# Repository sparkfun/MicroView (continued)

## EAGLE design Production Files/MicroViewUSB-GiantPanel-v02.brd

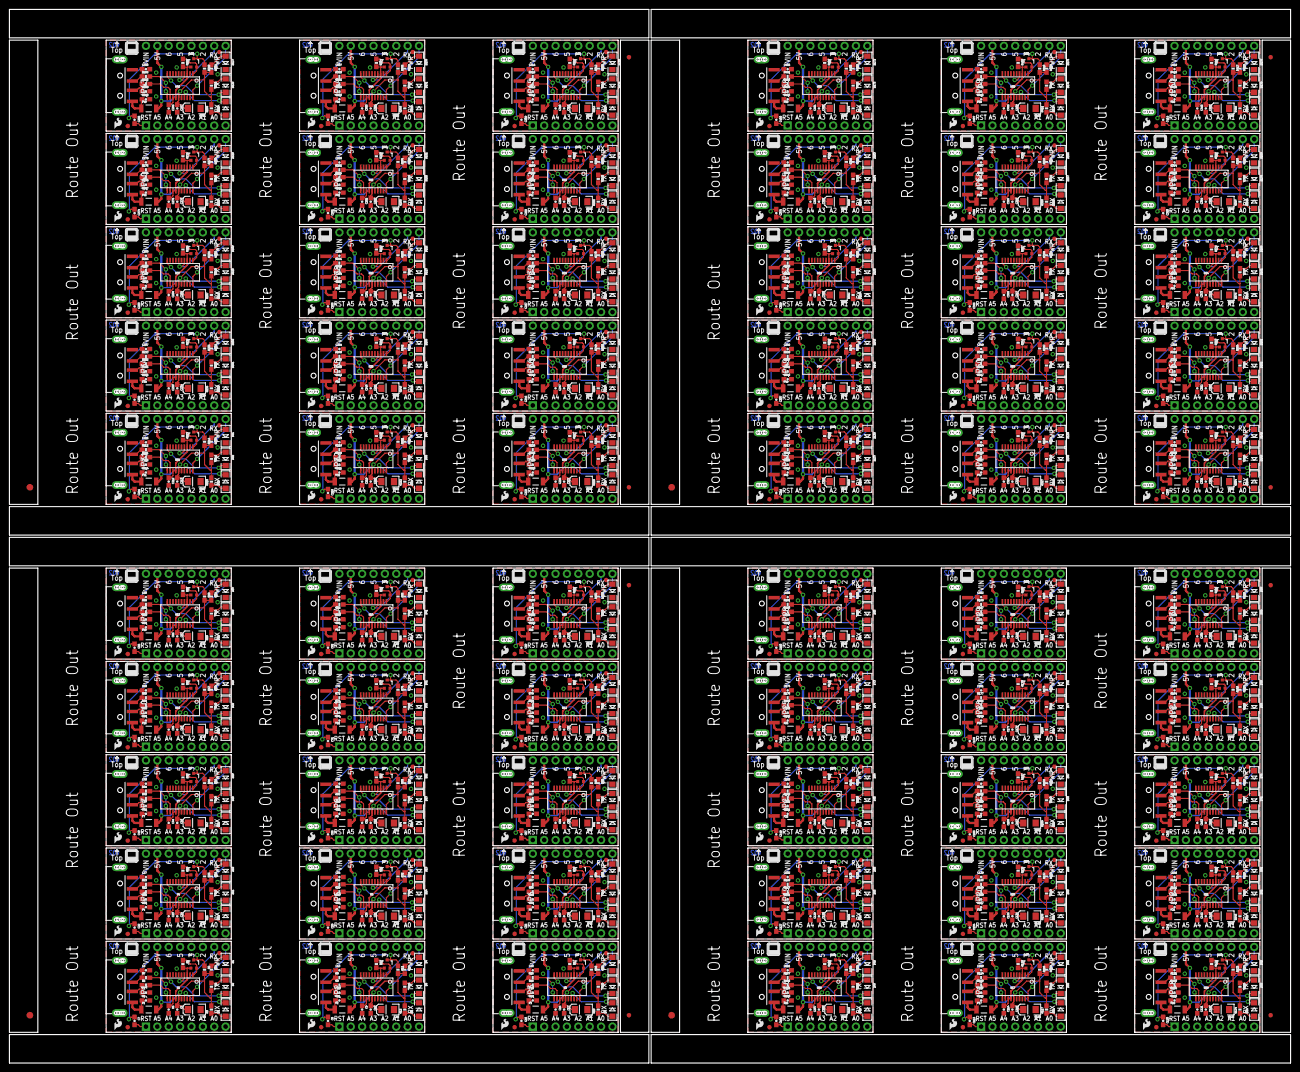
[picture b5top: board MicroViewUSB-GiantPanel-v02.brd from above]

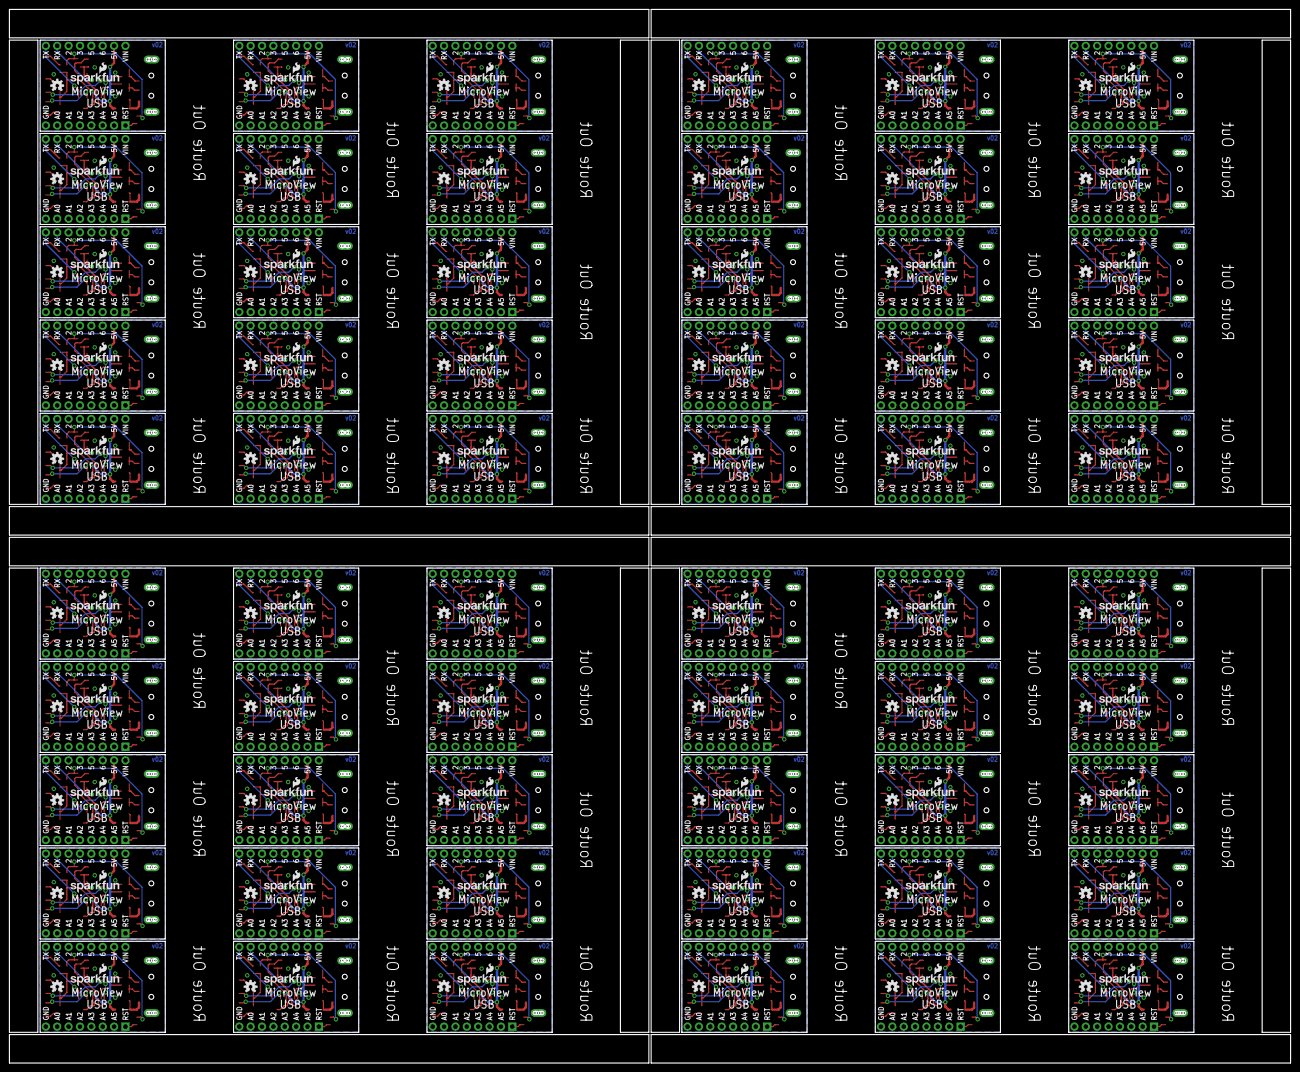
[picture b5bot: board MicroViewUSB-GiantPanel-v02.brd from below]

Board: 2 copper layers, 286.0 x 235.2 mm, 1632 parts (120 on the bottom side), 1080 nets.

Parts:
C1, C5, C6, C7, C8, C9, C10, C11, C15, C16, C17, C18, C22, C23, C24, C25, C29, C30, C31, C32, C36, C37, C38, C39, C43, C44, C45, C46, C50, C51, C52, C53, C57, C58, C59, C60, C64, C65, C66, C67, C71, C72, C73, C74, C78, C79, C80, C81, C85, C86, C87, C88, C92, C93, C94, C95, C99, C100, C101, C102, C106, C107, C108, C109, C113, C114, C115, C116, C120, C121, C122, C123, C127, C128, C129, C130, C134, C135, C136, C137, C141, C142, C143, C144, C148, C149, C150, C151, C155, C156, C157, C158, C162, C163, C164, C165, C169, C170, C171, C172, C176, C177, C178, C179, C183, C184, C185, C186, C190, C191, C192, C193, C197, C198, C199, C200, C204, C205, C206, C207, C211, C212, C213, C214, C218, C219, C220, C221, C225, C226, C227, C228, C232, C233, C234, C235, C239, C240, C241, C242, C246, C247, C248, C249, C253, C254, C255, C256, C260, C261, C262, C263, C267, C268, C269, C270, C274, C275, C276, C277, C281, C282, C283, C284, C288, C289, C290, C291, C295, C296, C297, C298, C302, C303, C304, C305, C309, C310, C311, C312, C316, C317, C318, C319, C323, C324, C325, C326, C330, C331, C332, C333, C337, C338, C339, C340, C344, C345, C346, C347, C351, C352, C353, C354, C358, C359, C360, C361, C365, C366, C367, C368, C372, C373, C374, C375, C379, C380, C381, C382, C386, C387, C388, C389, C393, C394, C395, C396, C400, C401, C402, C403, C407, C408, C409, C410, C414, C415, C416, C417: 0.1uF; 0603-CAP
C2, C3, C12, C13, C19, C20, C26, C27, C33, C34, C40, C41, C47, C48, C54, C55, C61, C62, C68, C69, C75, C76, C82, C83, C89, C90, C96, C97, C103, C104, C110, C111, C117, C118, C124, C125, C131, C132, C138, C139, C145, C146, C152, C153, C159, C160, C166, C167, C173, C174, C180, C181, C187, C188, C194, C195, C201, C202, C208, C209, C215, C216, C222, C223, C229, C230, C236, C237, C243, C244, C250, C251, C257, C258, C264, C265, C271, C272, C278, C279, C285, C286, C292, C293, C299, C300, C306, C307, C313, C314, C320, C321, C327, C328, C334, C335, C341, C342, C348, C349, C355, C356, C362, C363, C369, C370, C376, C377, C383, C384, C390, C391, C397, C398, C404, C405, C411, C412, C418, C419: 47pF; 0603-CAP
C4, C14, C21, C28, C35, C42, C49, C56, C63, C70, C77, C84, C91, C98, C105, C112, C119, C126, C133, C140, C147, C154, C161, C168, C175, C182, C189, C196, C203, C210, C217, C224, C231, C238, C245, C252, C259, C266, C273, C280, C287, C294, C301, C308, C315, C322, C329, C336, C343, C350, C357, C364, C371, C378, C385, C392, C399, C406, C413, C420: 10uF; EIA3216
D1, D4, D7, D10, D13, D16, D19, D22, D25, D28, D31, D34, D37, D40, D43, D46, D49, D52, D55, D58, D61, D64, D67, D70, D73, D76, D79, D82, D85, D88, D91, D94, D97, D100, D103, D106, D109, D112, D115, D118, D121, D124, D127, D130, D133, D136, D139, D142, D145, D148, D151, D154, D157, D160, D163, D166, D169, D172, D175, D178: GREEN; LED-1206
D2, D5, D8, D11, D14, D17, D20, D23, D26, D29, D32, D35, D38, D41, D44, D47, D50, D53, D56, D59, D62, D65, D68, D71, D74, D77, D80, D83, D86, D89, D92, D95, D98, D101, D104, D107, D110, D113, D116, D119, D122, D125, D128, D131, D134, D137, D140, D143, D146, D149, D152, D155, D158, D161, D164, D167, D170, D173, D176, D179: RED; LED-1206
D3, D6, D9, D12, D15, D18, D21, D24, D27, D30, D33, D36, D39, D42, D45, D48, D51, D54, D57, D60, D63, D66, D69, D72, D75, D78, D81, D84, D87, D90, D93, D96, D99, D102, D105, D108, D111, D114, D117, D120, D123, D126, D129, D132, D135, D138, D141, D144, D147, D150, D153, D156, D159, D162, D165, D168, D171, D174, D177, D180: Yellow; LED-1206
E$1, E$4, E$9, E$12: FIDUCIAL-1.5X3
E$2, E$3, E$5, E$6, E$7, E$8, E$10, E$11: FIDUCIAL-1X2
F1, F2, F3, F4, F5, F6, F7, F8, F9, F10, F11, F12, F13, F14, F15, F16, F17, F18, F19, F20, F21, F22, F23, F24, F25, F26, F27, F28, F29, F30, F31, F32, F33, F34, F35, F36, F37, F38, F39, F40, F41, F42, F43, F44, F45, F46, F47, F48, F49, F50, F51, F52, F53, F54, F55, F56, F57, F58, F59, F60: 500mA; PTC-1206-WIDE
FID1, FID2, FID3, FID4, FID5, FID6, FID7, FID8, FID9, FID10, FID11, FID12, FID13, FID14, FID15, FID16, FID17, FID18, FID19, FID20, FID21, FID22, FID23, FID24, FID25, FID26, FID27, FID28, FID29, FID30, FID31, FID32, FID33, FID34, FID35, FID36, FID37, FID38, FID39, FID40, FID41, FID42, FID43, FID44, FID45, FID46, FID47, FID48, FID49, FID50, FID51, FID52, FID53, FID54, FID55, FID56, FID57, FID58, FID59, FID60, FID61, FID62, FID63, FID64, FID65, FID66, FID67, FID68, FID69, FID70, FID71, FID72, FID73, FID74, FID75, FID76, FID77, FID78, FID79, FID80, FID81, FID82, FID83, FID84, FID85, FID86, FID87, FID88, FID89, FID90, FID91, FID92, FID93, FID94, FID95, FID96, FID97, FID98, FID99, FID100, FID101, FID102, FID103, FID104, FID105, FID106, FID107, FID108, FID109, FID110, FID111, FID112, FID113, FID114, FID115, FID116, FID117, FID118, FID119, FID120: FIDUCIAL1X2; FIDUCIAL-1X2
J1, J2, J3, J4, J5, J6, J7, J8, J9, J10, J11, J12, J13, J14, J15, J16, J17, J18, J19, J20, J21, J22, J23, J24, J25, J26, J27, J28, J29, J30, J31, J32, J33, J34, J35, J36, J37, J38, J39, J40, J41, J42, J43, J44, J45, J46, J47, J48, J49, J50, J51, J52, J53, J54, J55, J56, J57, J58, J59, J60: MICROVIEW-16ND; MV-DIP16-NODIMENSION
JP1, JP2, JP3, JP4, JP5, JP6, JP7, JP8, JP9, JP10, JP11, JP12, JP13, JP14, JP15, JP16, JP17, JP18, JP19, JP20, JP21, JP22, JP23, JP24, JP25, JP26, JP27, JP28, JP29, JP30, JP31, JP32, JP33, JP34, JP35, JP36, JP37, JP38, JP39, JP40, JP41, JP42, JP43, JP44, JP45, JP46, JP47, JP48, JP49, JP50, JP51, JP52, JP53, JP54, JP55, JP56, JP57, JP58, JP59, JP60: USBA-SMD-MALE; USB-A-SMT-MALE
LOGO1, LOGO5, LOGO8, LOGO11, LOGO14, LOGO17, LOGO20, LOGO23, LOGO26, LOGO29, LOGO32, LOGO35, LOGO38, LOGO41, LOGO44, LOGO47, LOGO50, LOGO53, LOGO56, LOGO59, LOGO62, LOGO65, LOGO68, LOGO71, LOGO74, LOGO77, LOGO80, LOGO83, LOGO86, LOGO89, LOGO92, LOGO95, LOGO98, LOGO101, LOGO104, LOGO107, LOGO110, LOGO113, LOGO116, LOGO119, LOGO122, LOGO125, LOGO128, LOGO131, LOGO134, LOGO137, LOGO140, LOGO143, LOGO146, LOGO149, LOGO152, LOGO155, LOGO158, LOGO161, LOGO164, LOGO167, LOGO170, LOGO173, LOGO176, LOGO179: SFE_LOGO_FLAME.1_INCH; SFE_LOGO_FLAME_.1
LOGO2, LOGO4, LOGO7, LOGO10, LOGO13, LOGO16, LOGO19, LOGO22, LOGO25, LOGO28, LOGO31, LOGO34, LOGO37, LOGO40, LOGO43, LOGO46, LOGO49, LOGO52, LOGO55, LOGO58, LOGO61, LOGO64, LOGO67, LOGO70, LOGO73, LOGO76, LOGO79, LOGO82, LOGO85, LOGO88, LOGO91, LOGO94, LOGO97, LOGO100, LOGO103, LOGO106, LOGO109, LOGO112, LOGO115, LOGO118, LOGO121, LOGO124, LOGO127, LOGO130, LOGO133, LOGO136, LOGO139, LOGO142, LOGO145, LOGO148, LOGO151, LOGO154, LOGO157, LOGO160, LOGO163, LOGO166, LOGO169, LOGO172, LOGO175, LOGO178: OSHW-LOGOS; OSHW-LOGO-S
LOGO3, LOGO6, LOGO9, LOGO12, LOGO15, LOGO18, LOGO21, LOGO24, LOGO27, LOGO30, LOGO33, LOGO36, LOGO39, LOGO42, LOGO45, LOGO48, LOGO51, LOGO54, LOGO57, LOGO60, LOGO63, LOGO66, LOGO69, LOGO72, LOGO75, LOGO78, LOGO81, LOGO84, LOGO87, LOGO90, LOGO93, LOGO96, LOGO99, LOGO102, LOGO105, LOGO108, LOGO111, LOGO114, LOGO117, LOGO120, LOGO123, LOGO126, LOGO129, LOGO132, LOGO135, LOGO138, LOGO141, LOGO144, LOGO147, LOGO150, LOGO153, LOGO156, LOGO159, LOGO162, LOGO165, LOGO168, LOGO171, LOGO174, LOGO177, LOGO180: SFE_LOGO_NAME_FLAME.1_INCH; SFE_LOGO_NAME_FLAME_.1
Q1, Q2, Q3, Q4, Q5, Q6, Q7, Q8, Q9, Q10, Q11, Q12, Q13, Q14, Q15, Q16, Q17, Q18, Q19, Q20, Q21, Q22, Q23, Q24, Q25, Q26, Q27, Q28, Q29, Q30, Q31, Q32, Q33, Q34, Q35, Q36, Q37, Q38, Q39, Q40, Q41, Q42, Q43, Q44, Q45, Q46, Q47, Q48, Q49, Q50, Q51, Q52, Q53, Q54, Q55, Q56, Q57, Q58, Q59, Q60: 2N7002PW; SOT323
R1, R2, R10, R11, R17, R18, R24, R25, R31, R32, R38, R39, R45, R46, R52, R53, R59, R60, R66, R67, R73, R74, R80, R81, R87, R88, R94, R95, R101, R102, R108, R109, R115, R116, R122, R123, R129, R130, R136, R137, R143, R144, R150, R151, R157, R158, R164, R165, R171, R172, R178, R179, R185, R186, R192, R193, R199, R200, R206, R207, R213, R214, R220, R221, R227, R228, R234, R235, R241, R242, R248, R249, R255, R256, R262, R263, R269, R270, R276, R277, R283, R284, R290, R291, R297, R298, R304, R305, R311, R312, R318, R319, R325, R326, R332, R333, R339, R340, R346, R347, R353, R354, R360, R361, R367, R368, R374, R375, R381, R382, R388, R389, R395, R396, R402, R403, R409, R410, R416, R417: 10K; 0603-RES
R3, R4, R5, R12, R13, R14, R19, R20, R21, R26, R27, R28, R33, R34, R35, R40, R41, R42, R47, R48, R49, R54, R55, R56, R61, R62, R63, R68, R69, R70, R75, R76, R77, R82, R83, R84, R89, R90, R91, R96, R97, R98, R103, R104, R105, R110, R111, R112, R117, R118, R119, R124, R125, R126, R131, R132, R133, R138, R139, R140, R145, R146, R147, R152, R153, R154, R159, R160, R161, R166, R167, R168, R173, R174, R175, R180, R181, R182, R187, R188, R189, R194, R195, R196, R201, R202, R203, R208, R209, R210, R215, R216, R217, R222, R223, R224, R229, R230, R231, R236, R237, R238, R243, R244, R245, R250, R251, R252, R257, R258, R259, R264, R265, R266, R271, R272, R273, R278, R279, R280, R285, R286, R287, R292, R293, R294, R299, R300, R301, R306, R307, R308, R313, R314, R315, R320, R321, R322, R327, R328, R329, R334, R335, R336, R341, R342, R343, R348, R349, R350, R355, R356, R357, R362, R363, R364, R369, R370, R371, R376, R377, R378, R383, R384, R385, R390, R391, R392, R397, R398, R399, R404, R405, R406, R411, R412, R413, R418, R419, R420: 1K; 0603-RES
R6, R7, R8, R9, R15, R16, R22, R23, R29, R30, R36, R37, R43, R44, R50, R51, R57, R58, R64, R65, R71, R72, R78, R79, R85, R86, R92, R93, R99, R100, R106, R107, R113, R114, R120, R121, R127, R128, R134, R135, R141, R142, R148, R149, R155, R156, R162, R163, R169, R170, R176, R177, R183, R184, R190, R191, R197, R198, R204, R205, R211, R212, R218, R219, R225, R226, R232, R233, R239, R240, R246, R247, R253, R254, R260, R261, R267, R268, R274, R275, R281, R282, R288, R289, R295, R296, R302, R303, R309, R310, R316, R317, R323, R324, R330, R331, R337, R338, R344, R345, R351, R352, R358, R359, R365, R366, R372, R373, R379, R380, R386, R387, R393, R394, R400, R401, R407, R408, R414, R415: 27; 0603-RES
U1, U2, U3, U4, U5, U6, U7, U8, U9, U10, U11, U12, U13, U14, U15, U16, U17, U18, U19, U20, U21, U22, U23, U24, U25, U26, U27, U28, U29, U30, U31, U32, U33, U34, U35, U36, U37, U38, U39, U40, U41, U42, U43, U44, U45, U46, U47, U48, U49, U50, U51, U52, U53, U54, U55, U56, U57, U58, U59, U60: FT231XS; SSOP20_L

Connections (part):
3.3V: C6.1, Q1.1, R1.2, U1.3, U1.13, U1.14
3.3V1: C9.1, Q2.1, R10.2, U2.3, U2.13, U2.14
3.3V2: C16.1, Q3.1, R17.2, U3.3, U3.13, U3.14
3.3V3: C23.1, Q4.1, R24.2, U4.3, U4.13, U4.14
3.3V4: C30.1, Q5.1, R31.2, U5.3, U5.13, U5.14
3.3V5: C37.1, Q6.1, R38.2, U6.3, U6.13, U6.14
3.3V6: C44.1, Q7.1, R45.2, U7.3, U7.13, U7.14
3.3V7: C51.1, Q8.1, R52.2, U8.3, U8.13, U8.14
3.3V8: C58.1, Q9.1, R59.2, U9.3, U9.13, U9.14
3.3V9: C65.1, Q10.1, R66.2, U10.3, U10.13, U10.14
3.3V10: C72.1, Q11.1, R73.2, U11.3, U11.13, U11.14
3.3V11: C79.1, Q12.1, R80.2, U12.3, U12.13, U12.14
3.3V12: C86.1, Q13.1, R87.2, U13.3, U13.13, U13.14
3.3V13: C93.1, Q14.1, R94.2, U14.3, U14.13, U14.14
3.3V14: C100.1, Q15.1, R101.2, U15.3, U15.13, U15.14
3.3V15: C107.1, Q16.1, R108.2, U16.3, U16.13, U16.14
3.3V16: C114.1, Q17.1, R115.2, U17.3, U17.13, U17.14
3.3V17: C121.1, Q18.1, R122.2, U18.3, U18.13, U18.14
3.3V18: C128.1, Q19.1, R129.2, U19.3, U19.13, U19.14
3.3V19: C135.1, Q20.1, R136.2, U20.3, U20.13, U20.14
3.3V20: C142.1, Q21.1, R143.2, U21.3, U21.13, U21.14
3.3V21: C149.1, Q22.1, R150.2, U22.3, U22.13, U22.14
3.3V22: C156.1, Q23.1, R157.2, U23.3, U23.13, U23.14
3.3V23: C163.1, Q24.1, R164.2, U24.3, U24.13, U24.14
3.3V24: C170.1, Q25.1, R171.2, U25.3, U25.13, U25.14
3.3V25: C177.1, Q26.1, R178.2, U26.3, U26.13, U26.14
3.3V26: C184.1, Q27.1, R185.2, U27.3, U27.13, U27.14
3.3V27: C191.1, Q28.1, R192.2, U28.3, U28.13, U28.14
3.3V28: C198.1, Q29.1, R199.2, U29.3, U29.13, U29.14
3.3V29: C205.1, Q30.1, R206.2, U30.3, U30.13, U30.14
3.3V30: C212.1, Q31.1, R213.2, U31.3, U31.13, U31.14
3.3V31: C219.1, Q32.1, R220.2, U32.3, U32.13, U32.14
3.3V32: C226.1, Q33.1, R227.2, U33.3, U33.13, U33.14
3.3V33: C233.1, Q34.1, R234.2, U34.3, U34.13, U34.14
3.3V34: C240.1, Q35.1, R241.2, U35.3, U35.13, U35.14
3.3V35: C247.1, Q36.1, R248.2, U36.3, U36.13, U36.14
3.3V36: C254.1, Q37.1, R255.2, U37.3, U37.13, U37.14
3.3V37: C261.1, Q38.1, R262.2, U38.3, U38.13, U38.14
3.3V38: C268.1, Q39.1, R269.2, U39.3, U39.13, U39.14
3.3V39: C275.1, Q40.1, R276.2, U40.3, U40.13, U40.14
3.3V40: C282.1, Q41.1, R283.2, U41.3, U41.13, U41.14
3.3V41: C289.1, Q42.1, R290.2, U42.3, U42.13, U42.14
3.3V42: C296.1, Q43.1, R297.2, U43.3, U43.13, U43.14
3.3V43: C303.1, Q44.1, R304.2, U44.3, U44.13, U44.14
3.3V44: C310.1, Q45.1, R311.2, U45.3, U45.13, U45.14
3.3V45: C317.1, Q46.1, R318.2, U46.3, U46.13, U46.14
3.3V46: C324.1, Q47.1, R325.2, U47.3, U47.13, U47.14
3.3V47: C331.1, Q48.1, R332.2, U48.3, U48.13, U48.14
3.3V48: C338.1, Q49.1, R339.2, U49.3, U49.13, U49.14
3.3V49: C345.1, Q50.1, R346.2, U50.3, U50.13, U50.14
3.3V50: C352.1, Q51.1, R353.2, U51.3, U51.13, U51.14
3.3V51: C359.1, Q52.1, R360.2, U52.3, U52.13, U52.14
3.3V52: C366.1, Q53.1, R367.2, U53.3, U53.13, U53.14
3.3V53: C373.1, Q54.1, R374.2, U54.3, U54.13, U54.14
3.3V54: C380.1, Q55.1, R381.2, U55.3, U55.13, U55.14
3.3V55: C387.1, Q56.1, R388.2, U56.3, U56.13, U56.14
3.3V56: C394.1, Q57.1, R395.2, U57.3, U57.13, U57.14
3.3V57: C401.1, Q58.1, R402.2, U58.3, U58.13, U58.14
3.3V58: C408.1, Q59.1, R409.2, U59.3, U59.13, U59.14
3.3V59: C415.1, Q60.1, R416.2, U60.3, U60.13, U60.14
5V: C4.A, C5.1, F1.2, J1.15, R2.2, R3.2, R4.2, R5.2, U1.15
5V1: C10.1, C14.A, F2.2, J2.15, R11.2, R12.2, R13.2, R14.2, U2.15
5V2: C17.1, C21.A, F3.2, J3.15, R18.2, R19.2, R20.2, R21.2, U3.15
5V3: C24.1, C28.A, F4.2, J4.15, R25.2, R26.2, R27.2, R28.2, U4.15
5V4: C31.1, C35.A, F5.2, J5.15, R32.2, R33.2, R34.2, R35.2, U5.15
5V5: C38.1, C42.A, F6.2, J6.15, R39.2, R40.2, R41.2, R42.2, U6.15
5V6: C45.1, C49.A, F7.2, J7.15, R46.2, R47.2, R48.2, R49.2, U7.15
5V7: C52.1, C56.A, F8.2, J8.15, R53.2, R54.2, R55.2, R56.2, U8.15
5V8: C59.1, C63.A, F9.2, J9.15, R60.2, R61.2, R62.2, R63.2, U9.15
5V9: C66.1, C70.A, F10.2, J10.15, R67.2, R68.2, R69.2, R70.2, U10.15
5V10: C73.1, C77.A, F11.2, J11.15, R74.2, R75.2, R76.2, R77.2, U11.15
5V11: C80.1, C84.A, F12.2, J12.15, R81.2, R82.2, R83.2, R84.2, U12.15
5V12: C87.1, C91.A, F13.2, J13.15, R88.2, R89.2, R90.2, R91.2, U13.15
5V13: C94.1, C98.A, F14.2, J14.15, R95.2, R96.2, R97.2, R98.2, U14.15
5V14: C101.1, C105.A, F15.2, J15.15, R102.2, R103.2, R104.2, R105.2, U15.15
5V15: C108.1, C112.A, F16.2, J16.15, R109.2, R110.2, R111.2, R112.2, U16.15
5V16: C115.1, C119.A, F17.2, J17.15, R116.2, R117.2, R118.2, R119.2, U17.15
5V17: C122.1, C126.A, F18.2, J18.15, R123.2, R124.2, R125.2, R126.2, U18.15
5V18: C129.1, C133.A, F19.2, J19.15, R130.2, R131.2, R132.2, R133.2, U19.15
5V19: C136.1, C140.A, F20.2, J20.15, R137.2, R138.2, R139.2, R140.2, U20.15
5V20: C143.1, C147.A, F21.2, J21.15, R144.2, R145.2, R146.2, R147.2, U21.15
5V21: C150.1, C154.A, F22.2, J22.15, R151.2, R152.2, R153.2, R154.2, U22.15
5V22: C157.1, C161.A, F23.2, J23.15, R158.2, R159.2, R160.2, R161.2, U23.15
5V23: C164.1, C168.A, F24.2, J24.15, R165.2, R166.2, R167.2, R168.2, U24.15
5V24: C171.1, C175.A, F25.2, J25.15, R172.2, R173.2, R174.2, R175.2, U25.15
5V25: C178.1, C182.A, F26.2, J26.15, R179.2, R180.2, R181.2, R182.2, U26.15
5V26: C185.1, C189.A, F27.2, J27.15, R186.2, R187.2, R188.2, R189.2, U27.15
5V27: C192.1, C196.A, F28.2, J28.15, R193.2, R194.2, R195.2, R196.2, U28.15
5V28: C199.1, C203.A, F29.2, J29.15, R200.2, R201.2, R202.2, R203.2, U29.15
5V29: C206.1, C210.A, F30.2, J30.15, R207.2, R208.2, R209.2, R210.2, U30.15
5V30: C213.1, C217.A, F31.2, J31.15, R214.2, R215.2, R216.2, R217.2, U31.15
5V31: C220.1, C224.A, F32.2, J32.15, R221.2, R222.2, R223.2, R224.2, U32.15
5V32: C227.1, C231.A, F33.2, J33.15, R228.2, R229.2, R230.2, R231.2, U33.15
5V33: C234.1, C238.A, F34.2, J34.15, R235.2, R236.2, R237.2, R238.2, U34.15
5V34: C241.1, C245.A, F35.2, J35.15, R242.2, R243.2, R244.2, R245.2, U35.15
5V35: C248.1, C252.A, F36.2, J36.15, R249.2, R250.2, R251.2, R252.2, U36.15
5V36: C255.1, C259.A, F37.2, J37.15, R256.2, R257.2, R258.2, R259.2, U37.15
5V37: C262.1, C266.A, F38.2, J38.15, R263.2, R264.2, R265.2, R266.2, U38.15
5V38: C269.1, C273.A, F39.2, J39.15, R270.2, R271.2, R272.2, R273.2, U39.15
5V39: C276.1, C280.A, F40.2, J40.15, R277.2, R278.2, R279.2, R280.2, U40.15
5V40: C283.1, C287.A, F41.2, J41.15, R284.2, R285.2, R286.2, R287.2, U41.15
5V41: C290.1, C294.A, F42.2, J42.15, R291.2, R292.2, R293.2, R294.2, U42.15
5V42: C297.1, C301.A, F43.2, J43.15, R298.2, R299.2, R300.2, R301.2, U43.15
5V43: C304.1, C308.A, F44.2, J44.15, R305.2, R306.2, R307.2, R308.2, U44.15
5V44: C311.1, C315.A, F45.2, J45.15, R312.2, R313.2, R314.2, R315.2, U45.15
5V45: C318.1, C322.A, F46.2, J46.15, R319.2, R320.2, R321.2, R322.2, U46.15
5V46: C325.1, C329.A, F47.2, J47.15, R326.2, R327.2, R328.2, R329.2, U47.15
5V47: C332.1, C336.A, F48.2, J48.15, R333.2, R334.2, R335.2, R336.2, U48.15
5V48: C339.1, C343.A, F49.2, J49.15, R340.2, R341.2, R342.2, R343.2, U49.15
5V49: C346.1, C350.A, F50.2, J50.15, R347.2, R348.2, R349.2, R350.2, U50.15
5V50: C353.1, C357.A, F51.2, J51.15, R354.2, R355.2, R356.2, R357.2, U51.15
5V51: C360.1, C364.A, F52.2, J52.15, R361.2, R362.2, R363.2, R364.2, U52.15
5V52: C367.1, C371.A, F53.2, J53.15, R368.2, R369.2, R370.2, R371.2, U53.15
5V53: C374.1, C378.A, F54.2, J54.15, R375.2, R376.2, R377.2, R378.2, U54.15
5V54: C381.1, C385.A, F55.2, J55.15, R382.2, R383.2, R384.2, R385.2, U55.15
5V55: C388.1, C392.A, F56.2, J56.15, R389.2, R390.2, R391.2, R392.2, U56.15
5V56: C395.1, C399.A, F57.2, J57.15, R396.2, R397.2, R398.2, R399.2, U57.15
5V57: C402.1, C406.A, F58.2, J58.15, R403.2, R404.2, R405.2, R406.2, U58.15
5V58: C409.1, C413.A, F59.2, J59.15, R410.2, R411.2, R412.2, R413.2, U59.15
5V59: C416.1, C420.A, F60.2, J60.15, R417.2, R418.2, R419.2, R420.2, U60.15
D+: C3.1, JP1.D+1, R7.1
D+1: C13.1, JP2.D+1, R9.1
D+2: C20.1, JP3.D+1, R16.1
D+3: C27.1, JP4.D+1, R23.1
D+4: C34.1, JP5.D+1, R30.1
D+5: C41.1, JP6.D+1, R37.1
D+6: C48.1, JP7.D+1, R44.1
D+7: C55.1, JP8.D+1, R51.1
D+8: C62.1, JP9.D+1, R58.1
D+9: C69.1, JP10.D+1, R65.1
D+10: C76.1, JP11.D+1, R72.1
D+11: C83.1, JP12.D+1, R79.1
D+12: C90.1, JP13.D+1, R86.1
D+13: C97.1, JP14.D+1, R93.1
D+14: C104.1, JP15.D+1, R100.1
D+15: C111.1, JP16.D+1, R107.1
D+16: C118.1, JP17.D+1, R114.1
D+17: C125.1, JP18.D+1, R121.1
D+18: C132.1, JP19.D+1, R128.1
D+19: C139.1, JP20.D+1, R135.1
D+20: C146.1, JP21.D+1, R142.1
D+21: C153.1, JP22.D+1, R149.1
D+22: C160.1, JP23.D+1, R156.1
D+23: C167.1, JP24.D+1, R163.1
D+24: C174.1, JP25.D+1, R170.1
D+25: C181.1, JP26.D+1, R177.1
D+26: C188.1, JP27.D+1, R184.1
D+27: C195.1, JP28.D+1, R191.1
D+28: C202.1, JP29.D+1, R198.1
D+29: C209.1, JP30.D+1, R205.1
D+30: C216.1, JP31.D+1, R212.1
D+31: C223.1, JP32.D+1, R219.1
D+32: C230.1, JP33.D+1, R226.1
D+33: C237.1, JP34.D+1, R233.1
D+34: C244.1, JP35.D+1, R240.1
D+35: C251.1, JP36.D+1, R247.1
D+36: C258.1, JP37.D+1, R254.1
D+37: C265.1, JP38.D+1, R261.1
D+38: C272.1, JP39.D+1, R268.1
D+39: C279.1, JP40.D+1, R275.1
D+40: C286.1, JP41.D+1, R282.1
D+41: C293.1, JP42.D+1, R289.1
D+42: C300.1, JP43.D+1, R296.1
D+43: C307.1, JP44.D+1, R303.1
D+44: C314.1, JP45.D+1, R310.1
D+45: C321.1, JP46.D+1, R317.1
D+46: C328.1, JP47.D+1, R324.1
D+47: C335.1, JP48.D+1, R331.1
D+48: C342.1, JP49.D+1, R338.1
D+49: C349.1, JP50.D+1, R345.1
D+50: C356.1, JP51.D+1, R352.1
D+51: C363.1, JP52.D+1, R359.1
D+52: C370.1, JP53.D+1, R366.1
D+53: C377.1, JP54.D+1, R373.1
D+54: C384.1, JP55.D+1, R380.1
D+55: C391.1, JP56.D+1, R387.1
D+56: C398.1, JP57.D+1, R394.1
D+57: C405.1, JP58.D+1, R401.1
D+58: C412.1, JP59.D+1, R408.1
D+59: C419.1, JP60.D+1, R415.1
D-: C2.1, JP1.D-1, R6.1
D-1: C12.1, JP2.D-1, R8.1
D-2: C19.1, JP3.D-1, R15.1
D-3: C26.1, JP4.D-1, R22.1
D-4: C33.1, JP5.D-1, R29.1
D-5: C40.1, JP6.D-1, R36.1
D-6: C47.1, JP7.D-1, R43.1
D-7: C54.1, JP8.D-1, R50.1
D-8: C61.1, JP9.D-1, R57.1
D-9: C68.1, JP10.D-1, R64.1
D-10: C75.1, JP11.D-1, R71.1
D-11: C82.1, JP12.D-1, R78.1
D-12: C89.1, JP13.D-1, R85.1
D-13: C96.1, JP14.D-1, R92.1
D-14: C103.1, JP15.D-1, R99.1
D-15: C110.1, JP16.D-1, R106.1
D-16: C117.1, JP17.D-1, R113.1
D-17: C124.1, JP18.D-1, R120.1
D-18: C131.1, JP19.D-1, R127.1
D-19: C138.1, JP20.D-1, R134.1
D-20: C145.1, JP21.D-1, R141.1
D-21: C152.1, JP22.D-1, R148.1
D-22: C159.1, JP23.D-1, R155.1
D-23: C166.1, JP24.D-1, R162.1
D-24: C173.1, JP25.D-1, R169.1
D-25: C180.1, JP26.D-1, R176.1
D-26: C187.1, JP27.D-1, R183.1
D-27: C194.1, JP28.D-1, R190.1
D-28: C201.1, JP29.D-1, R197.1
D-29: C208.1, JP30.D-1, R204.1
D-30: C215.1, JP31.D-1, R211.1
D-31: C222.1, JP32.D-1, R218.1
D-32: C229.1, JP33.D-1, R225.1
D-33: C236.1, JP34.D-1, R232.1
D-34: C243.1, JP35.D-1, R239.1
D-35: C250.1, JP36.D-1, R246.1
D-36: C257.1, JP37.D-1, R253.1
D-37: C264.1, JP38.D-1, R260.1
D-38: C271.1, JP39.D-1, R267.1
D-39: C278.1, JP40.D-1, R274.1
D-40: C285.1, JP41.D-1, R281.1
D-41: C292.1, JP42.D-1, R288.1
D-42: C299.1, JP43.D-1, R295.1
D-43: C306.1, JP44.D-1, R302.1
D-44: C313.1, JP45.D-1, R309.1
D-45: C320.1, JP46.D-1, R316.1
D-46: C327.1, JP47.D-1, R323.1
D-47: C334.1, JP48.D-1, R330.1
D-48: C341.1, JP49.D-1, R337.1
D-49: C348.1, JP50.D-1, R344.1
D-50: C355.1, JP51.D-1, R351.1
D-51: C362.1, JP52.D-1, R358.1
D-52: C369.1, JP53.D-1, R365.1
D-53: C376.1, JP54.D-1, R372.1
D-54: C383.1, JP55.D-1, R379.1
D-55: C390.1, JP56.D-1, R386.1
D-56: C397.1, JP57.D-1, R393.1
D-57: C404.1, JP58.D-1, R400.1
D-58: C411.1, JP59.D-1, R407.1
D-59: C418.1, JP60.D-1, R414.1
DTR: C7.1, Q1.3, R2.1
DTR1: C8.1, Q2.3, R11.1
DTR2: C15.1, Q3.3, R18.1
DTR3: C22.1, Q4.3, R25.1
DTR4: C29.1, Q5.3, R32.1
DTR5: C36.1, Q6.3, R39.1
DTR6: C43.1, Q7.3, R46.1
DTR7: C50.1, Q8.3, R53.1
DTR8: C57.1, Q9.3, R60.1
DTR9: C64.1, Q10.3, R67.1
DTR10: C71.1, Q11.3, R74.1
DTR11: C78.1, Q12.3, R81.1
DTR12: C85.1, Q13.3, R88.1
DTR13: C92.1, Q14.3, R95.1
DTR14: C99.1, Q15.3, R102.1
DTR15: C106.1, Q16.3, R109.1
DTR16: C113.1, Q17.3, R116.1
DTR17: C120.1, Q18.3, R123.1
DTR18: C127.1, Q19.3, R130.1
DTR19: C134.1, Q20.3, R137.1
DTR20: C141.1, Q21.3, R144.1
DTR21: C148.1, Q22.3, R151.1
DTR22: C155.1, Q23.3, R158.1
DTR23: C162.1, Q24.3, R165.1
DTR24: C169.1, Q25.3, R172.1
DTR25: C176.1, Q26.3, R179.1
DTR26: C183.1, Q27.3, R186.1
DTR27: C190.1, Q28.3, R193.1
DTR28: C197.1, Q29.3, R200.1
DTR29: C204.1, Q30.3, R207.1
DTR30: C211.1, Q31.3, R214.1
DTR31: C218.1, Q32.3, R221.1
DTR32: C225.1, Q33.3, R228.1
DTR33: C232.1, Q34.3, R235.1
DTR34: C239.1, Q35.3, R242.1
DTR35: C246.1, Q36.3, R249.1
DTR36: C253.1, Q37.3, R256.1
DTR37: C260.1, Q38.3, R263.1
DTR38: C267.1, Q39.3, R270.1
DTR39: C274.1, Q40.3, R277.1
DTR40: C281.1, Q41.3, R284.1
DTR41: C288.1, Q42.3, R291.1
DTR42: C295.1, Q43.3, R298.1
DTR43: C302.1, Q44.3, R305.1
DTR44: C309.1, Q45.3, R312.1
DTR45: C316.1, Q46.3, R319.1
DTR46: C323.1, Q47.3, R326.1
DTR47: C330.1, Q48.3, R333.1
DTR48: C337.1, Q49.3, R340.1
DTR49: C344.1, Q50.3, R347.1
DTR50: C351.1, Q51.3, R354.1
DTR51: C358.1, Q52.3, R361.1
DTR52: C365.1, Q53.3, R368.1
DTR53: C372.1, Q54.3, R375.1
DTR54: C379.1, Q55.3, R382.1
DTR55: C386.1, Q56.3, R389.1
DTR56: C393.1, Q57.3, R396.1
DTR57: C400.1, Q58.3, R403.1
DTR58: C407.1, Q59.3, R410.1
DTR59: C414.1, Q60.3, R417.1
GND: C1.2, C2.2, C3.2, C4.C, C5.2, C6.2, D1.C, J1.8, JP1.GND1, U1.6, U1.16
GND1: C9.2, C10.2, C11.2, C12.2, C13.2, C14.C, D4.C, J2.8, JP2.GND1, U2.6, U2.16
GND2: C16.2, C17.2, C18.2, C19.2, C20.2, C21.C, D7.C, J3.8, JP3.GND1, U3.6, U3.16
GND3: C23.2, C24.2, C25.2, C26.2, C27.2, C28.C, D10.C, J4.8, JP4.GND1, U4.6, U4.16
GND4: C30.2, C31.2, C32.2, C33.2, C34.2, C35.C, D13.C, J5.8, JP5.GND1, U5.6, U5.16
GND5: C37.2, C38.2, C39.2, C40.2, C41.2, C42.C, D16.C, J6.8, JP6.GND1, U6.6, U6.16
GND6: C44.2, C45.2, C46.2, C47.2, C48.2, C49.C, D19.C, J7.8, JP7.GND1, U7.6, U7.16
GND7: C51.2, C52.2, C53.2, C54.2, C55.2, C56.C, D22.C, J8.8, JP8.GND1, U8.6, U8.16
GND8: C58.2, C59.2, C60.2, C61.2, C62.2, C63.C, D25.C, J9.8, JP9.GND1, U9.6, U9.16
GND9: C65.2, C66.2, C67.2, C68.2, C69.2, C70.C, D28.C, J10.8, JP10.GND1, U10.6, U10.16
GND10: C72.2, C73.2, C74.2, C75.2, C76.2, C77.C, D31.C, J11.8, JP11.GND1, U11.6, U11.16
GND11: C79.2, C80.2, C81.2, C82.2, C83.2, C84.C, D34.C, J12.8, JP12.GND1, U12.6, U12.16
GND12: C86.2, C87.2, C88.2, C89.2, C90.2, C91.C, D37.C, J13.8, JP13.GND1, U13.6, U13.16
GND13: C93.2, C94.2, C95.2, C96.2, C97.2, C98.C, D40.C, J14.8, JP14.GND1, U14.6, U14.16
GND14: C100.2, C101.2, C102.2, C103.2, C104.2, C105.C, D43.C, J15.8, JP15.GND1, U15.6, U15.16
GND15: C107.2, C108.2, C109.2, C110.2, C111.2, C112.C, D46.C, J16.8, JP16.GND1, U16.6, U16.16
GND16: C114.2, C115.2, C116.2, C117.2, C118.2, C119.C, D49.C, J17.8, JP17.GND1, U17.6, U17.16
GND17: C121.2, C122.2, C123.2, C124.2, C125.2, C126.C, D52.C, J18.8, JP18.GND1, U18.6, U18.16
GND18: C128.2, C129.2, C130.2, C131.2, C132.2, C133.C, D55.C, J19.8, JP19.GND1, U19.6, U19.16
GND19: C135.2, C136.2, C137.2, C138.2, C139.2, C140.C, D58.C, J20.8, JP20.GND1, U20.6, U20.16
GND20: C142.2, C143.2, C144.2, C145.2, C146.2, C147.C, D61.C, J21.8, JP21.GND1, U21.6, U21.16
GND21: C149.2, C150.2, C151.2, C152.2, C153.2, C154.C, D64.C, J22.8, JP22.GND1, U22.6, U22.16
GND22: C156.2, C157.2, C158.2, C159.2, C160.2, C161.C, D67.C, J23.8, JP23.GND1, U23.6, U23.16
GND23: C163.2, C164.2, C165.2, C166.2, C167.2, C168.C, D70.C, J24.8, JP24.GND1, U24.6, U24.16
GND24: C170.2, C171.2, C172.2, C173.2, C174.2, C175.C, D73.C, J25.8, JP25.GND1, U25.6, U25.16
GND25: C177.2, C178.2, C179.2, C180.2, C181.2, C182.C, D76.C, J26.8, JP26.GND1, U26.6, U26.16
GND26: C184.2, C185.2, C186.2, C187.2, C188.2, C189.C, D79.C, J27.8, JP27.GND1, U27.6, U27.16
GND27: C191.2, C192.2, C193.2, C194.2, C195.2, C196.C, D82.C, J28.8, JP28.GND1, U28.6, U28.16
GND28: C198.2, C199.2, C200.2, C201.2, C202.2, C203.C, D85.C, J29.8, JP29.GND1, U29.6, U29.16
GND29: C205.2, C206.2, C207.2, C208.2, C209.2, C210.C, D88.C, J30.8, JP30.GND1, U30.6, U30.16
GND30: C212.2, C213.2, C214.2, C215.2, C216.2, C217.C, D91.C, J31.8, JP31.GND1, U31.6, U31.16
GND31: C219.2, C220.2, C221.2, C222.2, C223.2, C224.C, D94.C, J32.8, JP32.GND1, U32.6, U32.16
GND32: C226.2, C227.2, C228.2, C229.2, C230.2, C231.C, D97.C, J33.8, JP33.GND1, U33.6, U33.16
GND33: C233.2, C234.2, C235.2, C236.2, C237.2, C238.C, D100.C, J34.8, JP34.GND1, U34.6, U34.16
GND34: C240.2, C241.2, C242.2, C243.2, C244.2, C245.C, D103.C, J35.8, JP35.GND1, U35.6, U35.16
GND35: C247.2, C248.2, C249.2, C250.2, C251.2, C252.C, D106.C, J36.8, JP36.GND1, U36.6, U36.16
GND36: C254.2, C255.2, C256.2, C257.2, C258.2, C259.C, D109.C, J37.8, JP37.GND1, U37.6, U37.16
GND37: C261.2, C262.2, C263.2, C264.2, C265.2, C266.C, D112.C, J38.8, JP38.GND1, U38.6, U38.16
GND38: C268.2, C269.2, C270.2, C271.2, C272.2, C273.C, D115.C, J39.8, JP39.GND1, U39.6, U39.16
GND39: C275.2, C276.2, C277.2, C278.2, C279.2, C280.C, D118.C, J40.8, JP40.GND1, U40.6, U40.16
GND40: C282.2, C283.2, C284.2, C285.2, C286.2, C287.C, D121.C, J41.8, JP41.GND1, U41.6, U41.16
GND41: C289.2, C290.2, C291.2, C292.2, C293.2, C294.C, D124.C, J42.8, JP42.GND1, U42.6, U42.16
GND42: C296.2, C297.2, C298.2, C299.2, C300.2, C301.C, D127.C, J43.8, JP43.GND1, U43.6, U43.16
GND43: C303.2, C304.2, C305.2, C306.2, C307.2, C308.C, D130.C, J44.8, JP44.GND1, U44.6, U44.16
GND44: C310.2, C311.2, C312.2, C313.2, C314.2, C315.C, D133.C, J45.8, JP45.GND1, U45.6, U45.16
GND45: C317.2, C318.2, C319.2, C320.2, C321.2, C322.C, D136.C, J46.8, JP46.GND1, U46.6, U46.16
GND46: C324.2, C325.2, C326.2, C327.2, C328.2, C329.C, D139.C, J47.8, JP47.GND1, U47.6, U47.16
GND47: C331.2, C332.2, C333.2, C334.2, C335.2, C336.C, D142.C, J48.8, JP48.GND1, U48.6, U48.16
GND48: C338.2, C339.2, C340.2, C341.2, C342.2, C343.C, D145.C, J49.8, JP49.GND1, U49.6, U49.16
GND49: C345.2, C346.2, C347.2, C348.2, C349.2, C350.C, D148.C, J50.8, JP50.GND1, U50.6, U50.16
GND50: C352.2, C353.2, C354.2, C355.2, C356.2, C357.C, D151.C, J51.8, JP51.GND1, U51.6, U51.16
GND51: C359.2, C360.2, C361.2, C362.2, C363.2, C364.C, D154.C, J52.8, JP52.GND1, U52.6, U52.16
GND52: C366.2, C367.2, C368.2, C369.2, C370.2, C371.C, D157.C, J53.8, JP53.GND1, U53.6, U53.16
GND53: C373.2, C374.2, C375.2, C376.2, C377.2, C378.C, D160.C, J54.8, JP54.GND1, U54.6, U54.16
GND54: C380.2, C381.2, C382.2, C383.2, C384.2, C385.C, D163.C, J55.8, JP55.GND1, U55.6, U55.16
GND55: C387.2, C388.2, C389.2, C390.2, C391.2, C392.C, D166.C, J56.8, JP56.GND1, U56.6, U56.16
GND56: C394.2, C395.2, C396.2, C397.2, C398.2, C399.C, D169.C, J57.8, JP57.GND1, U57.6, U57.16
GND57: C401.2, C402.2, C403.2, C404.2, C405.2, C406.C, D172.C, J58.8, JP58.GND1, U58.6, U58.16
GND58: C408.2, C409.2, C410.2, C411.2, C412.2, C413.C, D175.C, J59.8, JP59.GND1, U59.6, U59.16
GND59: C415.2, C416.2, C417.2, C418.2, C419.2, C420.C, D178.C, J60.8, JP60.GND1, U60.6, U60.16
unnamed: D1.A, R5.1
unnamed: C7.2, J1.1
unnamed: D5.A, R13.1
unnamed: D6.A, R12.1
unnamed: R8.2, U2.12
unnamed: R6.2, U1.12
unnamed: R7.2, U1.11
unnamed: D2.A, R4.1
unnamed: R9.2, U2.11
unnamed: D3.A, R3.1
unnamed: Q2.2, R10.1, U2.1
unnamed: Q1.2, R1.1, U1.1
unnamed: D4.A, R14.1
unnamed: C8.2, J2.1
unnamed: D8.A, R20.1
unnamed: D9.A, R19.1
unnamed: R15.2, U3.12
unnamed: R16.2, U3.11
unnamed: Q3.2, R17.1, U3.1
unnamed: D7.A, R21.1
unnamed: C15.2, J3.1
unnamed: D11.A, R27.1
unnamed: D12.A, R26.1
unnamed: R22.2, U4.12
unnamed: R23.2, U4.11
unnamed: Q4.2, R24.1, U4.1
unnamed: D10.A, R28.1
unnamed: C22.2, J4.1
unnamed: D14.A, R34.1
unnamed: D15.A, R33.1
unnamed: R29.2, U5.12
unnamed: R30.2, U5.11
unnamed: Q5.2, R31.1, U5.1
unnamed: D13.A, R35.1
unnamed: C29.2, J5.1
unnamed: D17.A, R41.1
unnamed: D18.A, R40.1
unnamed: R36.2, U6.12
unnamed: R37.2, U6.11
unnamed: Q6.2, R38.1, U6.1
unnamed: D16.A, R42.1
unnamed: C36.2, J6.1
unnamed: D20.A, R48.1
unnamed: D21.A, R47.1
unnamed: R43.2, U7.12
unnamed: R44.2, U7.11
unnamed: Q7.2, R45.1, U7.1
unnamed: D19.A, R49.1
unnamed: C43.2, J7.1
unnamed: D23.A, R55.1
unnamed: D24.A, R54.1
unnamed: R50.2, U8.12
unnamed: R51.2, U8.11
unnamed: Q8.2, R52.1, U8.1
unnamed: D22.A, R56.1
unnamed: C50.2, J8.1
unnamed: D26.A, R62.1
unnamed: D27.A, R61.1
unnamed: R57.2, U9.12
unnamed: R58.2, U9.11
unnamed: Q9.2, R59.1, U9.1
unnamed: D25.A, R63.1
unnamed: C57.2, J9.1
unnamed: D29.A, R69.1
unnamed: D30.A, R68.1
unnamed: R64.2, U10.12
unnamed: R65.2, U10.11
unnamed: Q10.2, R66.1, U10.1
unnamed: D28.A, R70.1
unnamed: C64.2, J10.1
unnamed: D32.A, R76.1
unnamed: D33.A, R75.1
unnamed: R71.2, U11.12
unnamed: R72.2, U11.11
unnamed: Q11.2, R73.1, U11.1
unnamed: D31.A, R77.1
unnamed: C71.2, J11.1
unnamed: D35.A, R83.1
unnamed: D36.A, R82.1
unnamed: R78.2, U12.12
unnamed: R79.2, U12.11
unnamed: Q12.2, R80.1, U12.1
unnamed: D34.A, R84.1
unnamed: C78.2, J12.1
unnamed: D38.A, R90.1
unnamed: D39.A, R89.1
unnamed: R85.2, U13.12
unnamed: R86.2, U13.11
unnamed: Q13.2, R87.1, U13.1
unnamed: D37.A, R91.1
unnamed: C85.2, J13.1
unnamed: D41.A, R97.1
unnamed: D42.A, R96.1
unnamed: R92.2, U14.12
unnamed: R93.2, U14.11
unnamed: Q14.2, R94.1, U14.1
unnamed: D40.A, R98.1
unnamed: C92.2, J14.1
unnamed: D44.A, R104.1
unnamed: D45.A, R103.1
unnamed: R99.2, U15.12
unnamed: R100.2, U15.11
unnamed: Q15.2, R101.1, U15.1
unnamed: D43.A, R105.1
unnamed: C99.2, J15.1
unnamed: D47.A, R111.1
unnamed: D48.A, R110.1
unnamed: R106.2, U16.12
unnamed: R107.2, U16.11
unnamed: Q16.2, R108.1, U16.1
unnamed: D46.A, R112.1
unnamed: C106.2, J16.1
unnamed: D50.A, R118.1
unnamed: D51.A, R117.1
unnamed: R113.2, U17.12
unnamed: R114.2, U17.11
unnamed: Q17.2, R115.1, U17.1
unnamed: D49.A, R119.1
unnamed: C113.2, J17.1
unnamed: D53.A, R125.1
unnamed: D54.A, R124.1
unnamed: R120.2, U18.12
unnamed: R121.2, U18.11
unnamed: Q18.2, R122.1, U18.1
unnamed: D52.A, R126.1
unnamed: C120.2, J18.1
unnamed: D56.A, R132.1
unnamed: D57.A, R131.1
unnamed: R127.2, U19.12
unnamed: R128.2, U19.11
unnamed: Q19.2, R129.1, U19.1
unnamed: D55.A, R133.1
unnamed: C127.2, J19.1
unnamed: D59.A, R139.1
unnamed: D60.A, R138.1
unnamed: R134.2, U20.12
unnamed: R135.2, U20.11
unnamed: Q20.2, R136.1, U20.1
unnamed: D58.A, R140.1
unnamed: C134.2, J20.1
unnamed: D62.A, R146.1
unnamed: D63.A, R145.1
unnamed: R141.2, U21.12
unnamed: R142.2, U21.11
unnamed: Q21.2, R143.1, U21.1
unnamed: D61.A, R147.1
unnamed: C141.2, J21.1
unnamed: D65.A, R153.1
unnamed: D66.A, R152.1
unnamed: R148.2, U22.12
unnamed: R149.2, U22.11
unnamed: Q22.2, R150.1, U22.1
unnamed: D64.A, R154.1
unnamed: C148.2, J22.1
unnamed: D68.A, R160.1
unnamed: D69.A, R159.1
unnamed: R155.2, U23.12
unnamed: R156.2, U23.11
unnamed: Q23.2, R157.1, U23.1
unnamed: D67.A, R161.1
unnamed: C155.2, J23.1
unnamed: D71.A, R167.1
unnamed: D72.A, R166.1
unnamed: R162.2, U24.12
unnamed: R163.2, U24.11
unnamed: Q24.2, R164.1, U24.1
unnamed: D70.A, R168.1
unnamed: C162.2, J24.1
unnamed: D74.A, R174.1
unnamed: D75.A, R173.1
unnamed: R169.2, U25.12
unnamed: R170.2, U25.11
unnamed: Q25.2, R171.1, U25.1
unnamed: D73.A, R175.1
unnamed: C169.2, J25.1
unnamed: D77.A, R181.1
unnamed: D78.A, R180.1
unnamed: R176.2, U26.12
unnamed: R177.2, U26.11
unnamed: Q26.2, R178.1, U26.1
unnamed: D76.A, R182.1
unnamed: C176.2, J26.1
unnamed: D80.A, R188.1
unnamed: D81.A, R187.1
unnamed: R183.2, U27.12
unnamed: R184.2, U27.11
unnamed: Q27.2, R185.1, U27.1
unnamed: D79.A, R189.1
unnamed: C183.2, J27.1
unnamed: D83.A, R195.1
unnamed: D84.A, R194.1
unnamed: R190.2, U28.12
unnamed: R191.2, U28.11
unnamed: Q28.2, R192.1, U28.1
unnamed: D82.A, R196.1
unnamed: C190.2, J28.1
unnamed: D86.A, R202.1
unnamed: D87.A, R201.1
unnamed: R197.2, U29.12
unnamed: R198.2, U29.11
unnamed: Q29.2, R199.1, U29.1
unnamed: D85.A, R203.1
unnamed: C197.2, J29.1
unnamed: D89.A, R209.1
unnamed: D90.A, R208.1
unnamed: R204.2, U30.12
unnamed: R205.2, U30.11
unnamed: Q30.2, R206.1, U30.1
unnamed: D88.A, R210.1
unnamed: C204.2, J30.1
unnamed: D92.A, R216.1
unnamed: D93.A, R215.1
unnamed: R211.2, U31.12
unnamed: R212.2, U31.11
unnamed: Q31.2, R213.1, U31.1
unnamed: D91.A, R217.1
unnamed: C211.2, J31.1
unnamed: D95.A, R223.1
unnamed: D96.A, R222.1
unnamed: R218.2, U32.12
unnamed: R219.2, U32.11
unnamed: Q32.2, R220.1, U32.1
unnamed: D94.A, R224.1
unnamed: C218.2, J32.1
unnamed: D98.A, R230.1
unnamed: D99.A, R229.1
unnamed: R225.2, U33.12
unnamed: R226.2, U33.11
unnamed: Q33.2, R227.1, U33.1
unnamed: D97.A, R231.1
unnamed: C225.2, J33.1
unnamed: D101.A, R237.1
unnamed: D102.A, R236.1
unnamed: R232.2, U34.12
unnamed: R233.2, U34.11
unnamed: Q34.2, R234.1, U34.1
unnamed: D100.A, R238.1
unnamed: C232.2, J34.1
unnamed: D104.A, R244.1
unnamed: D105.A, R243.1
unnamed: R239.2, U35.12
unnamed: R240.2, U35.11
unnamed: Q35.2, R241.1, U35.1
unnamed: D103.A, R245.1
unnamed: C239.2, J35.1
unnamed: D107.A, R251.1
unnamed: D108.A, R250.1
unnamed: R246.2, U36.12
unnamed: R247.2, U36.11
unnamed: Q36.2, R248.1, U36.1
unnamed: D106.A, R252.1
unnamed: C246.2, J36.1
unnamed: D110.A, R258.1
unnamed: D111.A, R257.1
unnamed: R253.2, U37.12
unnamed: R254.2, U37.11
unnamed: Q37.2, R255.1, U37.1
unnamed: D109.A, R259.1
unnamed: C253.2, J37.1
unnamed: D113.A, R265.1
unnamed: D114.A, R264.1
unnamed: R260.2, U38.12
unnamed: R261.2, U38.11
unnamed: Q38.2, R262.1, U38.1
unnamed: D112.A, R266.1
unnamed: C260.2, J38.1
unnamed: D116.A, R272.1
unnamed: D117.A, R271.1
unnamed: R267.2, U39.12
unnamed: R268.2, U39.11
unnamed: Q39.2, R269.1, U39.1
unnamed: D115.A, R273.1
unnamed: C267.2, J39.1
unnamed: D119.A, R279.1
unnamed: D120.A, R278.1
unnamed: R274.2, U40.12
unnamed: R275.2, U40.11
unnamed: Q40.2, R276.1, U40.1
unnamed: D118.A, R280.1
unnamed: C274.2, J40.1
unnamed: D122.A, R286.1
unnamed: D123.A, R285.1
unnamed: R281.2, U41.12
unnamed: R282.2, U41.11
unnamed: Q41.2, R283.1, U41.1
unnamed: D121.A, R287.1
unnamed: C281.2, J41.1
unnamed: D125.A, R293.1
unnamed: D126.A, R292.1
unnamed: R288.2, U42.12
unnamed: R289.2, U42.11
unnamed: Q42.2, R290.1, U42.1
unnamed: D124.A, R294.1
unnamed: C288.2, J42.1
unnamed: D128.A, R300.1
unnamed: D129.A, R299.1
unnamed: R295.2, U43.12
unnamed: R296.2, U43.11
unnamed: Q43.2, R297.1, U43.1
unnamed: D127.A, R301.1
unnamed: C295.2, J43.1
unnamed: D131.A, R307.1
unnamed: D132.A, R306.1
unnamed: R302.2, U44.12
unnamed: R303.2, U44.11
unnamed: Q44.2, R304.1, U44.1
unnamed: D130.A, R308.1
unnamed: C302.2, J44.1
unnamed: D134.A, R314.1
unnamed: D135.A, R313.1
unnamed: R309.2, U45.12
unnamed: R310.2, U45.11
unnamed: Q45.2, R311.1, U45.1
unnamed: D133.A, R315.1
unnamed: C309.2, J45.1
unnamed: D137.A, R321.1
unnamed: D138.A, R320.1
unnamed: R316.2, U46.12
unnamed: R317.2, U46.11
unnamed: Q46.2, R318.1, U46.1
unnamed: D136.A, R322.1
unnamed: C316.2, J46.1
unnamed: D140.A, R328.1
unnamed: D141.A, R327.1
unnamed: R323.2, U47.12
unnamed: R324.2, U47.11
unnamed: Q47.2, R325.1, U47.1
unnamed: D139.A, R329.1
unnamed: C323.2, J47.1
unnamed: D143.A, R335.1
unnamed: D144.A, R334.1
unnamed: R330.2, U48.12
unnamed: R331.2, U48.11
unnamed: Q48.2, R332.1, U48.1
unnamed: D142.A, R336.1
unnamed: C330.2, J48.1
unnamed: D146.A, R342.1
unnamed: D147.A, R341.1
unnamed: R337.2, U49.12
unnamed: R338.2, U49.11
unnamed: Q49.2, R339.1, U49.1
unnamed: D145.A, R343.1
unnamed: C337.2, J49.1
unnamed: D149.A, R349.1
unnamed: D150.A, R348.1
unnamed: R344.2, U50.12
unnamed: R345.2, U50.11
unnamed: Q50.2, R346.1, U50.1
unnamed: D148.A, R350.1
unnamed: C344.2, J50.1
unnamed: D152.A, R356.1
unnamed: D153.A, R355.1
unnamed: R351.2, U51.12
unnamed: R352.2, U51.11
unnamed: Q51.2, R353.1, U51.1
unnamed: D151.A, R357.1
unnamed: C351.2, J51.1
unnamed: D155.A, R363.1
unnamed: D156.A, R362.1
unnamed: R358.2, U52.12
unnamed: R359.2, U52.11
unnamed: Q52.2, R360.1, U52.1
unnamed: D154.A, R364.1
unnamed: C358.2, J52.1
unnamed: D158.A, R370.1
unnamed: D159.A, R369.1
unnamed: R365.2, U53.12
unnamed: R366.2, U53.11
unnamed: Q53.2, R367.1, U53.1
unnamed: D157.A, R371.1
unnamed: C365.2, J53.1
unnamed: D161.A, R377.1
unnamed: D162.A, R376.1
unnamed: R372.2, U54.12
unnamed: R373.2, U54.11
unnamed: Q54.2, R374.1, U54.1
unnamed: D160.A, R378.1
unnamed: C372.2, J54.1
unnamed: D164.A, R384.1
unnamed: D165.A, R383.1
unnamed: R379.2, U55.12
unnamed: R380.2, U55.11
unnamed: Q55.2, R381.1, U55.1
unnamed: D163.A, R385.1
unnamed: C379.2, J55.1
unnamed: D167.A, R391.1
unnamed: D168.A, R390.1
unnamed: R386.2, U56.12
unnamed: R387.2, U56.11
unnamed: Q56.2, R388.1, U56.1
unnamed: D166.A, R392.1
unnamed: C386.2, J56.1
unnamed: D170.A, R398.1
unnamed: D171.A, R397.1
unnamed: R393.2, U57.12
unnamed: R394.2, U57.11
unnamed: Q57.2, R395.1, U57.1
unnamed: D169.A, R399.1
unnamed: C393.2, J57.1
unnamed: D173.A, R405.1
unnamed: D174.A, R404.1
unnamed: R400.2, U58.12
unnamed: R401.2, U58.11
unnamed: Q58.2, R402.1, U58.1
unnamed: D172.A, R406.1
unnamed: C400.2, J58.1
unnamed: D176.A, R412.1
unnamed: D177.A, R411.1
unnamed: R407.2, U59.12
unnamed: R408.2, U59.11
unnamed: Q59.2, R409.1, U59.1
unnamed: D175.A, R413.1
unnamed: C407.2, J59.1
unnamed: D179.A, R419.1
unnamed: D180.A, R418.1
unnamed: R414.2, U60.12
unnamed: R415.2, U60.11
unnamed: Q60.2, R416.1, U60.1
unnamed: D178.A, R420.1
unnamed: C414.2, J60.1
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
